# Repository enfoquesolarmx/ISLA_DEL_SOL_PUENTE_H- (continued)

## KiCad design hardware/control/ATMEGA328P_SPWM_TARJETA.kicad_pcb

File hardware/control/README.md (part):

# Tarjeta de control V0.1: el cerebro de la Isla del Sol

La tarjeta de control lleva **dos microcontroladores** (módulos Arduino Nano con ATmega328P) y todo lo que necesitan alrededor:
- la alimentación de 48 V a 15, 8 y 5 V;
- los sensores de voltaje, corriente y temperatura;
- el corte del PWM por hardware;
- las órdenes a la tarjeta de transferencia;
- el CAN con el BMS, la pantalla, el ventilador y el buzzer.

> **Para quien arma y repara en la trinchera:** este documento es un **glosario de módulos**. Cada bloque de la tarjeta dice **qué hace**, **por qué existe**, **por qué cada pieza tiene ese valor** y **qué pasa si esa pieza falla**. Cuando algo no funcione, busca el bloque, mide en su test point y compara con la tabla.

*Vista superior en 3D (KiCad 9), serigrafía "TARJETA DE CONTROL SPWM · ISLA DEL SOL · VER 0.1.J.G NOV 2026". Los dos microcontroladores van en zócalo (aquí se ven los zócalos vacíos), igual que el 74HC08. La serigrafía indica el uso de cada conector, los valores de referencia y los sustitutos de trinchera.*

*Esquemático por bloques (KiCad 9, hoja A2). Cada marco azul es uno de los módulos de este glosario.*

---

## 0. Mapa de la tarjeta

| # | Módulo | Microcontrolador | Decisión | En una frase |
| --- | --- | --- | --- | --- |
| 1 | [Microcontroladores CRÍTICO y AUX](#1-microcontroladores-crítico-y-aux) · [**Mapa de pines**](#11-mapa-de-pines) | — | DC-010, DC-012, DC-017 | El CRÍTICO genera la onda y protege; el AUX informa y conversa |
| 2 | [Entrada de 48 V y su protección](#2-entrada-de-48-v-y-su-protección) | — | DC-003 | Que un pico de la batería no queme el buck |
| 3 | [Buck 48 → 15 V (XL7015)](#3-buck-48--15-v-xl7015) | — | DC-002 | El riel de drivers, relés y ventilador |
| 4 | [Buck 15 → 8 V (MP1584)](#4-buck-15--8-v-mp1584) | — | DC-004 | Baja el voltaje para que el 7805 vaya frío |
| 5 | [Regulador 5 V (7805)](#5-regulador-5-v-7805) | — | DC-005 | 5 V limpio: es la referencia del ADC |
| 6 | [Tablero de LEDs y test points](#6-tablero-de-leds-y-test-points) | — | DC-008 | Dónde está la falla y qué tan mal está |
| 7 | [Monitor del riel de 15 V](#7-monitor-del-riel-de-15-v) | AUX (A1) | DC-008 | Ve envejecer la fuente antes de que falle |
| 8 | [Sensado AC del inversor](#8-sensado-ac-del-inversor-y-de-la-red) | CRÍTICO (A0) | DC-006 | Lazo de amplitud de la salida |
| 9 | [Sensado AC de la red](#8-sensado-ac-del-inversor-y-de-la-red) | CRÍTICO (A6) | DC-006 | Sincronía antes de transferir |
| 10 | [Corriente AC con pinza SCT-013](#9-corriente-ac-con-pinza-sct-013-015) | CRÍTICO (A2) | DC-013 | Watts, sobrecarga y tiempo muerto |
| 11 | [Voltaje de batería](#10-voltaje-de-batería) | CRÍTICO (A3) | DC-007 | Bajo voltaje y estado de carga |
| 12 | [Temperatura (NTC)](#11-temperatura-ntc-10-k) | CRÍTICO (A1) | — | Derrateo y paro por calor |
| 13 | [Corte del PWM por hardware](#12-corte-del-pwm-por-hardware) | CRÍTICO / AUX | DC-014 | Apaga los MOSFET sin esperar al firmware |
| 14 | [Lectura de P9](#13-lectura-de-p9-tiempo-muerto) | CRÍTICO (A7) | DC-011 | Qué gate driver hay y qué tiempo muerto pide |
| 15 | [Límite de corriente I_LIM](#14-límite-de-corriente-i_lim) | CRÍTICO (D2) | DC-016 | Deja arrancar motores sin disparar el corte |
| 16 | [Órdenes a la tarjeta de transferencia (J15)](#15-órdenes-a-la-tarjeta-de-transferencia-j15) | CRÍTICO (D4–D6) | DC-019 | Red, inversor, cargador y unión N–PE |
| 17 | [Caída automática a la red](#16-caída-automática-a-la-red) | — | DC-019 | Si el inversor se corta, la casa vuelve a la red sola |
| 18 | [CAN con el BMS](#17-can-con-el-bms) | AUX (SPI) | DC-010 | Lo que la batería permite cargar y descargar |
| 19 | [Pantalla LCD y botonera](#18-pantalla-lcd-162-y-botonera) | AUX (D4, D5, A7) | — | Menú del SETUP y estado |
| 20 | [Ventilador](#19-ventilador) | AUX (D6) | — | Enfría el puente H |
| 21 | [Buzzer y LED de alarma](#20-buzzer-y-led-de-alarma) | AUX (D8) | — | Avisa sin que nadie mire la pantalla |
| 22 | [Salidas de 15 V y 5 V](#21-salidas-de-15-v-y-5-v) | — | — | Alimentan los gate drivers y módulos externos |

**Regla general de las resistencias de 1 kΩ en serie:** casi todas las señales que salen de la tarjeta por un cable pasan por **1 kΩ antes del pin del microcontrolador** (R3, R15, R19, R22, R25, R38, R39, R41). Si el cable se pela contra 15 V o recibe un pico, esa resistencia limita la corriente que entra a los diodos internos del ATmega a unos pocos mA, y el pin sobrevive. **No se quitan "porque sobran".**

**Regla general de las resistencias de 10 kΩ a GND (pull-down) o a 5 V (pull-up):** fijan el estado de una línea cuando nadie la maneja: microcontrolador en reset, cable suelto, módulo ausente. **El estado que fijan es siempre el seguro:** apagado, sin orden o casa en la red.

---

## 1. Microcontroladores CRÍTICO y AUX

> **Lo que decide la onda y la protege vive en un solo microcontrolador. Lo que informa y conversa vive en el otro.** (DC-010)

| Ref. | Valor | Qué hace | Por qué |
| --- | --- | --- | --- |
| **A1** | Arduino Nano (ATmega328P), **CRÍTICO** | SPWM (D9, D10, D11, D3), sensado AC y DC, relés, corte, P9, I_LIM | Todo lo que tiene que ocurrir **dentro del periodo de la portadora** de 24 kHz. No puede depender de un enlace |
| **A2** | Arduino Nano (ATmega328P), **AUX** | CAN/BMS, LCD, botonera, ventilador, buzzer, SENSOR_OK, AUX_KILL, monitor de 15 V | Lo que no es tiempo real. Si se cuelga, la onda sigue y el CRÍTICO protege solo |
| **R10, R11** | 4.7 kΩ a 5 V | Pull-ups del enlace I2C entre los dos (A4/A5) | El I2C es de drenaje abierto: sin pull-up nunca sube. 4.7 kΩ da un flanco de ~0.4 µs (máximo permitido 1 µs a 100 kHz). **Un solo par para todo el bus** |
| **C15, C19** | 1 µF | Desacople junto al pin +5V de cada Nano | Los Nano se alimentan por **+5V (pin 27), nunca por VIN** (DC-012): VIN pasa por otro regulador que necesita ≥7 V. El 1 µF da la corriente de los picos de conmutación del chip |

- **Los dos van en zócalo:** se cambian sin soldar, y el mismo zócalo acepta un **Nano Every (ATmega4809)** con otro firmware (DC-017, DC-018).
- **Si el enlace I2C se cae:** el AUX manda un latido cada ~100 ms. Si el CRÍTICO no lo recibe en ~500 ms, **deja de cargar** y sigue protegiendo la batería con su propia lectura.

### 1.1 Mapa de pines

> **Fuente de verdad para el firmware.** Verificado pin por pin contra el esquemático (`ATMEGA328P_SPWM_TARJETA.kicad_sch`, 2026-11-13): cada red de esta tabla es la que tiene el pin en KiCad. Si cambia el esquemático, **se actualiza esta tabla en el mismo cambio**.

**Columnas:**
- **Al encender:** cómo debe quedar el pin desde la primera línea de `setup()`, antes que cualquier otra cosa.
- **Dueño:** el timer o periférico que lo controla; ningún otro módulo del firmware debe tocarlo.

#### CRÍTICO (A1): tiempo real, SPWM y protección

| Pin | Red (KiCad) | Función | E/S | Al encender | Dueño | Sección |
| --- | --- | --- | --- | --- | --- | --- |
| D0 / D1 | — | Puerto serie (USB, carga del firmware, reporte) | — | Libre para `Serial` | USART | — |
| **D2** | `CRIT_D2_ILIM` | **I_LIM:** 0 V = en el límite de corriente → bajar la modulación | Entrada (INT0) | Entrada, **sin** pull-up interno (R40 externo) | INT0 | [14](#14-límite-de-corriente-i_lim) |
| **D3** | `LB_IN` | **LB:** pierna B, lado bajo (60/50 Hz) → 74HC08 | Salida | **BAJO** | ISR del Timer1 | [12](#12-corte-del-pwm-por-hardware) |
| **D4** | `INV_D4` | **INV_CMD:** la casa pasa al inversor (K4 + K2), vía R39 | Salida | **BAJO** (casa en la red) | Lógica de transferencia | [15](#15-órdenes-a-la-tarjeta-de-transferencia-j15), [16](#16-caída-automática-a-la-red) |
| **D5** | `CARG_CMD` | **CARG_CMD:** el transformador se conecta a la red para cargar (K1 + K3) | Salida | **BAJO** | Lógica de transferencia | [15](#15-órdenes-a-la-tarjeta-de-transferencia-j15) |
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
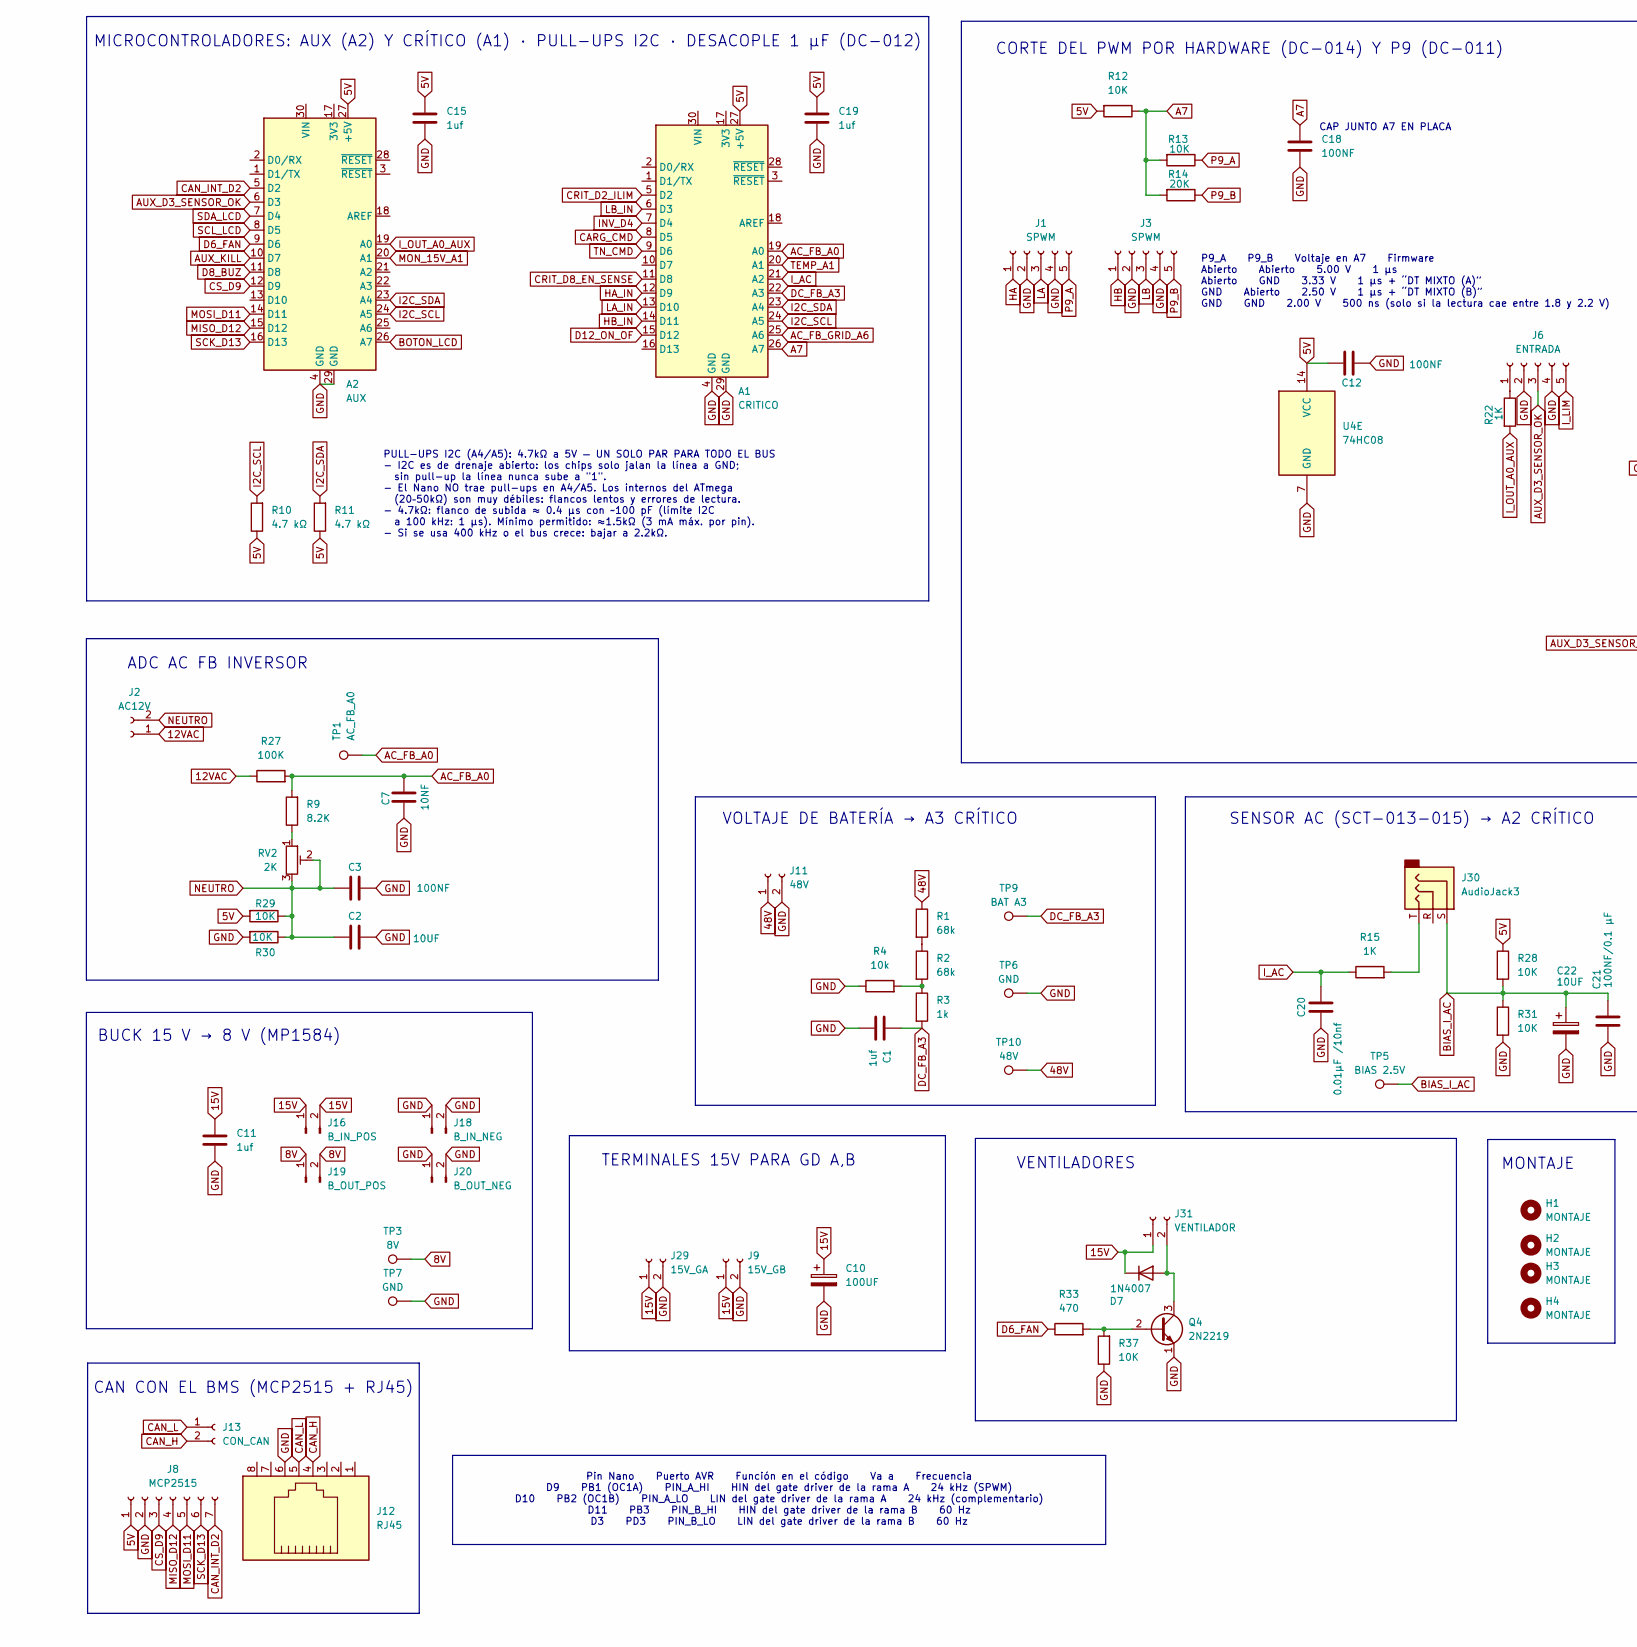
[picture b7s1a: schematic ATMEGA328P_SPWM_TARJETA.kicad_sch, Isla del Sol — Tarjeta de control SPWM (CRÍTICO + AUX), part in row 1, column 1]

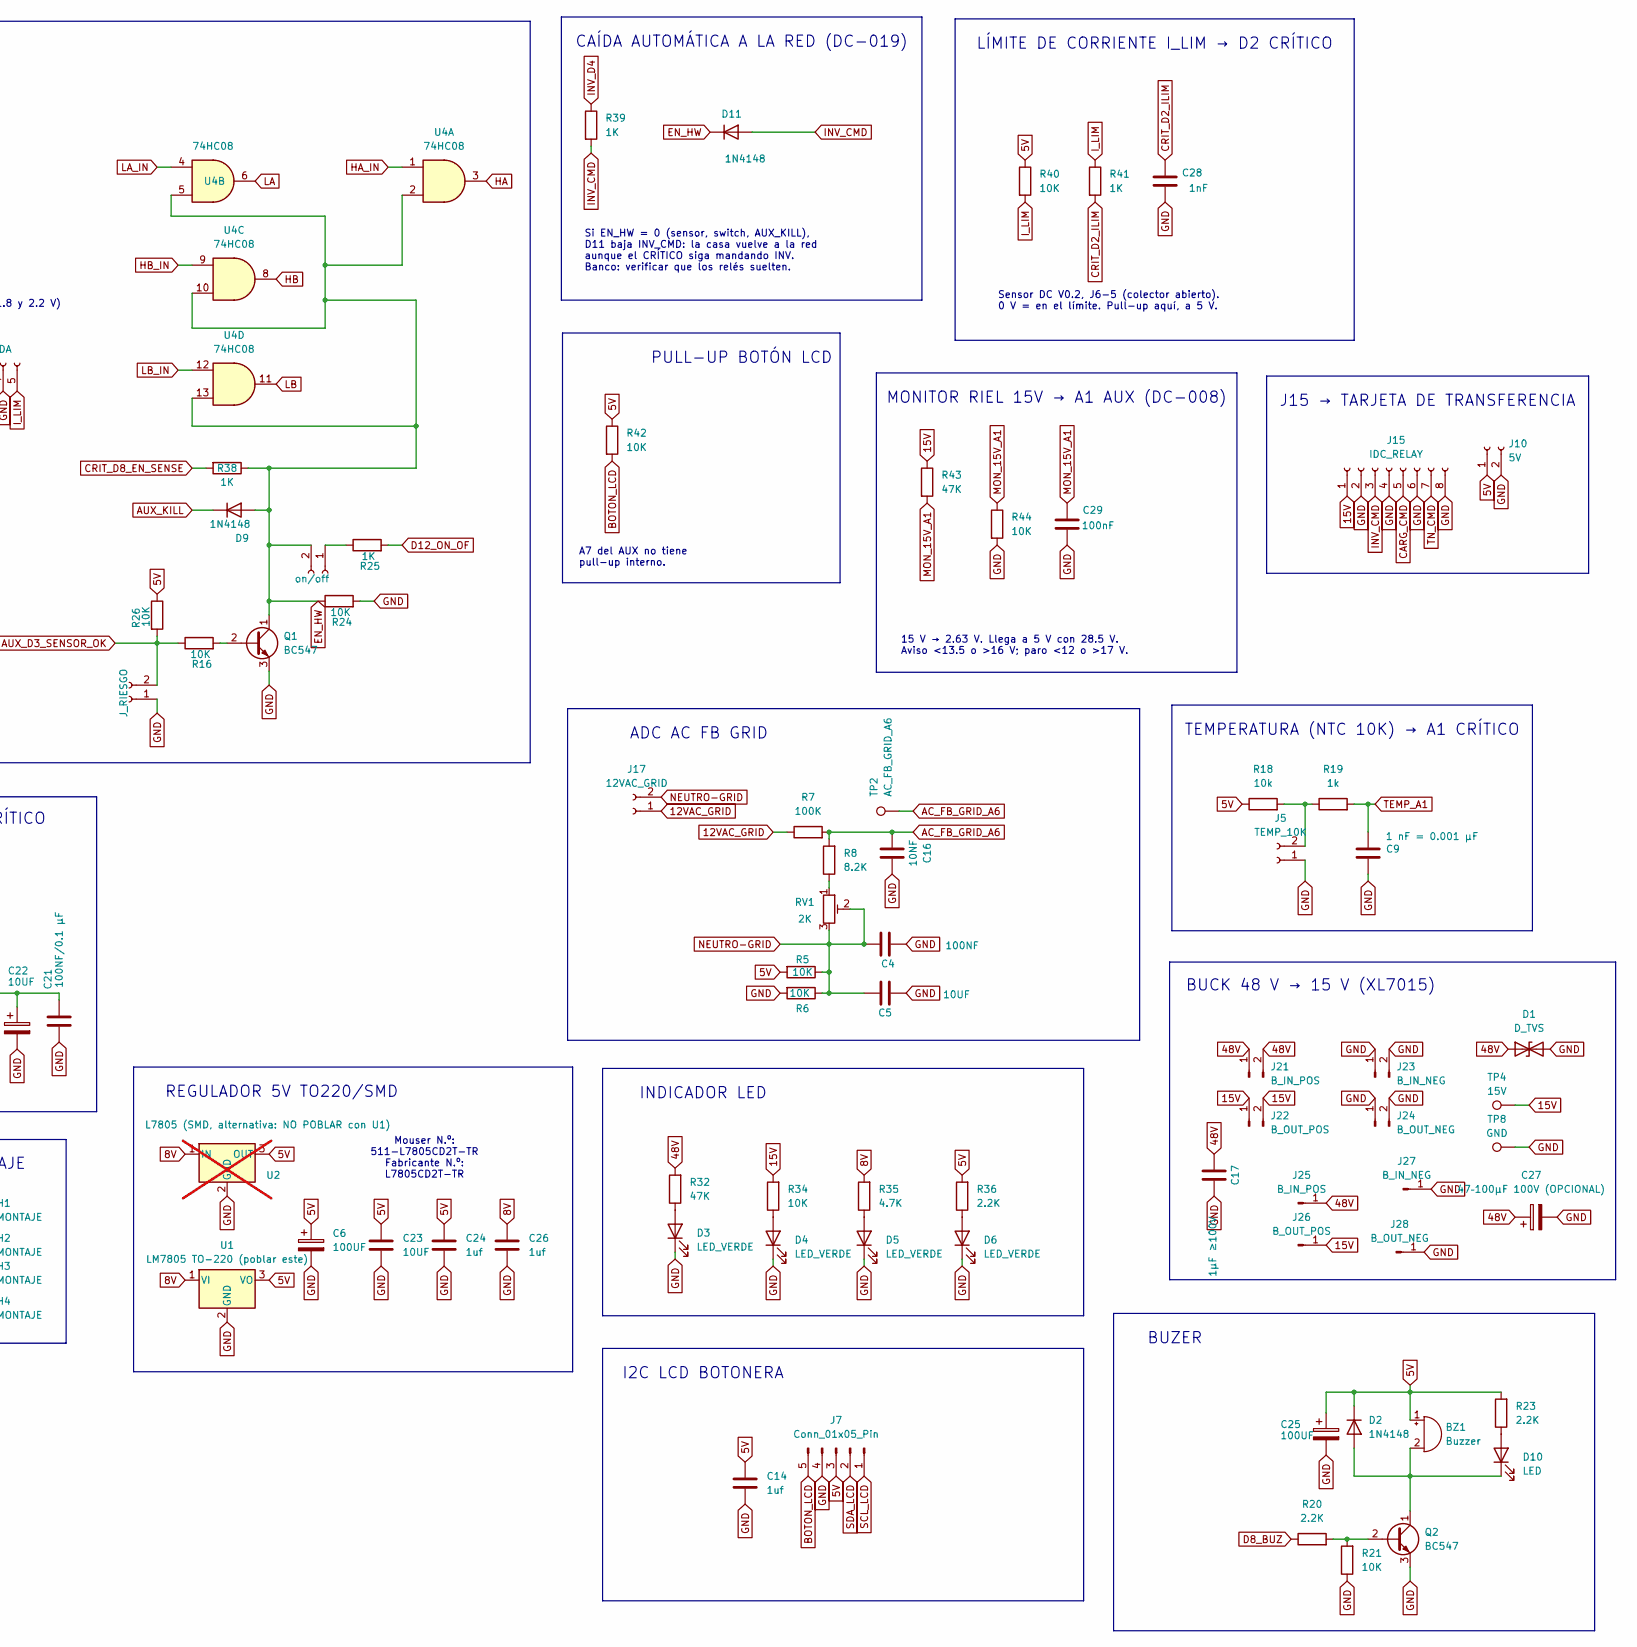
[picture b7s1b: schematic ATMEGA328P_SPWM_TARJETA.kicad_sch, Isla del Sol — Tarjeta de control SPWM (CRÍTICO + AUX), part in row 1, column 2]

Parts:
A1: CRITICO; Arduino_Nano
A2: AUX; Arduino_Nano
BZ1: Buzzer; Buzzer_12x9.5RM7.6
C1, C11, C14, C15, C19, C24, C26: 1uf; C_1206_3216Metric
C2, C5, C23: 10UF; C_1206_3216Metric
C3, C4, C18: 100NF; C_1206_3216Metric
C6, C10: 100UF; CP_Radial_D10.0mm_P5.00mm
C7, C16: 10NF; C_1206_3216Metric
C9: 1 nF = 0.001 µF; C_Disc_D3.0mm_W2.0mm_P2.50mm
C12: 100NF; C_Disc_D3.0mm_W2.0mm_P2.50mm
C17: 1µF ≥100V; C_1210_3225Metric_Pad1.33x2.70mm_HandSolder
C20: 0.01µF /10nf; C_Disc_D3.0mm_W1.6mm_P2.50mm
C21: 100NF/0.1 µF; C_Disc_D3.0mm_W1.6mm_P2.50mm
C22: 10UF; CP_Radial_D8.0mm_P3.50mm
C25: 100UF; CP_Radial_D8.0mm_P3.50mm
C27: 47–100µF 100V (OPCIONAL); CP_Elec_10x10
C28: 1nF; C_Disc_D3.0mm_W2.0mm_P2.50mm
C29: 100nF; C_Disc_D3.0mm_W2.0mm_P2.50mm
D1: D_TVS; D_SMB
D2, D9, D11: 1N4148; D_DO-35_SOD27_P7.62mm_Horizontal
D3, D4, D5, D6: LED_VERDE; LED_1206_3216Metric
D7: 1N4007; D_DO-41_SOD81_P10.16mm_Horizontal
D10: LED; LED_D3.0mm_Clear
H1, H2, H3, H4: MONTAJE; MountingHole_2.7mm_M2.5
J1, J3: SPWM; PhoenixContact_SPT_1.5_5-H-3.5_1x05_P3.5mm_Horizontal
J2: AC12V; TerminalBlock_MaiXu_MX126-5.0-02P_1x02_P5.00mm
J4: on/off; PinHeader_1x02_P2.54mm_Vertical
J5: TEMP_10K; PinHeader_1x02_P2.54mm_Vertical
J6: ENTRADA; PhoenixContact_SPT_1.5_5-H-3.5_1x05_P3.5mm_Horizontal
J7: Conn_01x05_Pin; PinHeader_1x05_P2.54mm_Vertical
J8: MCP2515; PinHeader_1x07_P2.54mm_Vertical
J9: 15V_GB; JST_EH_B2B-EH-A_1x02_P2.50mm_Vertical
J10: 5V; JST_EH_B2B-EH-A_1x02_P2.50mm_Vertical
J11: 48V; TerminalBlock_MaiXu_MX126-5.0-02P_1x02_P5.00mm
J12: RJ45; RJ45_OST_PJ012-8P8CX_Vertical
J13: CON_CAN; PinHeader_1x02_P2.54mm_Vertical
J14: J_RIESGO; PinHeader_1x02_P2.54mm_Vertical
J15: IDC_RELAY; IDC-Header_2x04_P2.54mm_Vertical
J16, J21: B_IN_POS; PinHeader_1x02_P2.54mm_Vertical
J17: 12VAC_GRID; TerminalBlock_MaiXu_MX126-5.0-02P_1x02_P5.00mm
J18, J23: B_IN_NEG; PinHeader_1x02_P2.54mm_Vertical
J19, J22: B_OUT_POS; PinHeader_1x02_P2.54mm_Vertical
J20, J24: B_OUT_NEG; PinHeader_1x02_P2.54mm_Vertical
J25: B_IN_POS; PinHeader_1x01_P2.54mm_Vertical
J26: B_OUT_POS; PinHeader_1x01_P2.54mm_Vertical
J27: B_IN_NEG; PinHeader_1x01_P2.54mm_Vertical
J28: B_OUT_NEG; PinHeader_1x01_P2.54mm_Vertical
J29: 15V_GA; JST_EH_B2B-EH-A_1x02_P2.50mm_Vertical
J30: AudioJack3; Jack_3.5mm_CUI_SJ1-3533NG_Horizontal_CircularHoles
J31: VENTILADOR; JST_EH_B2B-EH-A_1x02_P2.50mm_Vertical
Q1: BC547; TO-92_Inline
Q2: BC547; TO-92_Inline_Wide
Q4: 2N2219; TO-39-3
R1, R2: 68k; R_Axial_DIN0204_L3.6mm_D1.6mm_P5.08mm_Horizontal
R3, R19: 1k; R_Axial_DIN0204_L3.6mm_D1.6mm_P5.08mm_Horizontal
R4, R18: 10k; R_Axial_DIN0204_L3.6mm_D1.6mm_P5.08mm_Horizontal
R5, R6, R12, R13, R16, R21, R24, R26, R28, R29, R30, R31, R34, R37, R40, R42, R44: 10K; R_Axial_DIN0204_L3.6mm_D1.6mm_P5.08mm_Horizontal
R7, R27: 100K; R_Axial_DIN0204_L3.6mm_D1.6mm_P5.08mm_Horizontal
R8, R9: 8.2K; R_Axial_DIN0204_L3.6mm_D1.6mm_P5.08mm_Horizontal
R10, R11: 4.7 kΩ; R_Axial_DIN0204_L3.6mm_D1.6mm_P5.08mm_Horizontal
R14: 20K; R_Axial_DIN0204_L3.6mm_D1.6mm_P5.08mm_Horizontal
R15, R22, R25, R38, R39, R41: 1K; R_Axial_DIN0204_L3.6mm_D1.6mm_P5.08mm_Horizontal
R20, R23, R36: 2.2K; R_Axial_DIN0204_L3.6mm_D1.6mm_P5.08mm_Horizontal
R32, R43: 47K; R_Axial_DIN0204_L3.6mm_D1.6mm_P5.08mm_Horizontal
R33: 470; R_Axial_DIN0204_L3.6mm_D1.6mm_P5.08mm_Horizontal
R35: 4.7K; R_Axial_DIN0204_L3.6mm_D1.6mm_P5.08mm_Horizontal
RV1, RV2: 2K; Potentiometer_Bourns_3296W_Vertical
TP1: AC_FB_A0; TestPoint_Loop_D2.50mm_Drill1.0mm_LowProfile
TP2: AC_FB_GRID_A6; TestPoint_Loop_D2.50mm_Drill1.0mm_LowProfile
TP3: 8V; TestPoint_Loop_D2.50mm_Drill1.0mm_LowProfile
TP4: 15V; TestPoint_Loop_D2.50mm_Drill1.0mm_LowProfile
TP5: BIAS 2.5V; TestPoint_Loop_D2.50mm_Drill1.0mm_LowProfile
TP6, TP7, TP8: GND; TestPoint_Loop_D2.50mm_Drill1.0mm_LowProfile
TP9: BAT A3; TestPoint_Loop_D2.50mm_Drill1.0mm_LowProfile
TP10: 48V; TestPoint_Loop_D2.50mm_Drill1.0mm_LowProfile
U1: LM7805 TO-220 (poblar este); TO-220-3_Horizontal_TabDown
U2: L7805 (SMD, alternativa: NO POBLAR con U1); TO-252-2; not fitted
U4: 74HC08; DIP-14_W7.62mm_Socket

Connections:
5V: A1.27 (+5V), A2.27 (+5V), BZ1.1 (+), C6.1, C12.1, C14.1, C15.1, C19.1, C23.1, C24.1, C25.1, D2.1 (K), J7.3, J8.1, J10.1, R5.2, R10.1, R11.1, R12.2, R18.1, R23.2, R26.1, R28.1, R29.2, R36.2, R40.1, R42.1, U1.3 (VO), U2.3 (OUT), U4.14 (VCC)
8V: C26.1, J19.1, J19.2, R35.2, TP3.1, U1.1 (VI), U2.1 (IN)
12VAC: J2.1, R27.1
12VAC_GRID: J17.1, R7.1
15V: C10.1, C11.1, D7.1 (K), J9.1, J15.1, J16.1, J16.2, J22.1, J22.2, J26.1, J29.1, J31.1, R34.2, R43.1, TP4.1
48V: C17.1, C27.1, D1.1 (A1), J11.1, J21.1, J21.2, J25.1, R1.1, R32.2, TP10.1
A7: A1.26 (A7), C18.1, R12.1, R13.2, R14.2
AC_FB_A0: A1.19 (A0), C7.1, R9.2, R27.2, TP1.1
AC_FB_GRID_A6: A1.25 (A6), C16.1, R7.2, R8.2, TP2.1
AUX_D3_SENSOR_OK: A2.6 (D3), J6.3, J14.2, R16.1, R26.2
AUX_KILL: A2.10 (D7), D9.1 (K)
BIAS_I_AC: C21.1, C22.1, J30.S, R28.2, R31.1, TP5.1
BOTON_LCD: A2.26 (A7), J7.5, R42.2
CAN_H: J12.4, J13.2
CAN_INT_D2: A2.5 (D2), J8.7
CAN_L: J12.5, J13.1
CARG_CMD: A1.8 (D5), J15.5
CRIT_D2_ILIM: A1.5 (D2), C28.1, R41.2
CRIT_D8_EN_SENSE: A1.11 (D8), R38.2
CS_D9: A2.12 (D9), J8.3
D6_FAN: A2.9 (D6), R33.1
D8_BUZ: A2.11 (D8), R20.1
D12_ON_OF: A1.15 (D12), R25.2
DC_FB_A3: A1.22 (A3), C1.1, R3.2, TP9.1
EN_HW: D9.2 (A), D11.1 (K), J4.2, Q1.1 (C), R24.1, R38.1, U4.2, U4.5, U4.10, U4.13
GND: A1.4 (GND), A1.29 (GND), A2.4 (GND), A2.29 (GND), C1.2, C2.2, C3.2, C4.2, C5.2, C6.2, C7.2, C9.2, C10.2, C11.2, C12.2, C14.2, C15.2, C16.2, C17.2, C18.2, C19.2, C20.2, C21.2, C22.2, C23.2, C24.2, C25.2, C26.2, C27.2, C28.2, C29.2, D1.2 (A2), D3.1 (K), D4.1 (K), D5.1 (K), D6.1 (K), J1.2, J1.4, J3.2, J3.4, J5.1, J6.2, J6.4, J7.4, J8.2, J9.2, J10.2, J11.2, J12.6, J14.1, J15.2, J15.4, J15.6, J15.8, J18.1, J18.2, J20.1, J20.2, J23.1, J23.2, J24.1, J24.2, J27.1, J28.1, J29.2, Q1.3 (E), Q2.3 (E), Q4.1 (E), R4.1, R6.2, R21.1, R24.2, R30.2, R31.2, R37.1, R44.2, TP6.1, TP7.1, TP8.1, U1.2 (GND), U2.2 (GND), U4.7 (GND)
HA: J1.1, U4.3
HA_IN: A1.12 (D9), U4.1
HB: J3.1, U4.8
HB_IN: A1.14 (D11), U4.9
I2C_SCL: A1.24 (A5), A2.24 (A5), R10.2
I2C_SDA: A1.23 (A4), A2.23 (A4), R11.2
INV_CMD: D11.2 (A), J15.3, R39.2
INV_D4: A1.7 (D4), R39.1
I_AC: A1.21 (A2), C20.1, R15.1
I_LIM: J6.5, R40.2, R41.1
I_OUT_A0_AUX: A2.19 (A0), R22.2
LA: J1.3, U4.6
LA_IN: A1.13 (D10), U4.4
LB: J3.3, U4.11
LB_IN: A1.6 (D3), U4.12
MISO_D12: A2.15 (D12), J8.4
MON_15V_A1: A2.20 (A1), C29.1, R43.2, R44.1
MOSI_D11: A2.14 (D11), J8.5
NEUTRO: C2.1, C3.1, J2.2, R29.1, R30.1, RV2.2, RV2.3
NEUTRO-GRID: C4.1, C5.1, J17.2, R5.1, R6.1, RV1.2, RV1.3
unnamed: BZ1.2 (-), D2.2 (A), D10.1 (K), Q2.1 (C)
unnamed: D3.2 (A), R32.1
unnamed: D4.2 (A), R34.1
unnamed: D5.2 (A), R35.1
unnamed: D6.2 (A), R36.1
unnamed: D7.2 (A), J31.2, Q4.3 (C)
unnamed: D10.2 (A), R23.1
unnamed: J4.1, R25.1
unnamed: J5.2, R18.2, R19.1
unnamed: J6.1, R22.1
unnamed: J30.T, R15.2
unnamed: Q1.2 (B), R16.2
unnamed: Q2.2 (B), R20.2, R21.2
unnamed: Q4.2 (B), R33.2, R37.2
unnamed: R1.2, R2.1
unnamed: R2.2, R3.1, R4.2
unnamed: R8.1, RV1.1
unnamed: R9.1, RV2.1
P9_A: J1.5, R13.1
P9_B: J3.5, R14.1
SCK_D13: A2.16 (D13), J8.6
SCL_LCD: A2.8 (D5), J7.1
SDA_LCD: A2.7 (D4), J7.2
TEMP_A1: A1.20 (A1), C9.1, R19.2
TN_CMD: A1.9 (D6), J15.7

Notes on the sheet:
MONTAJE
TERMINALES 15V PARA GD A,B
Mouser N.º: 511-L7805CD2T-TR Fabricante N.º: L7805CD2T-TR
BUZER
P9_A P9_B Voltaje en A7 Firmware Abierto Abierto 5.00 V 1 µs Abierto GND 3.33 V 1 µs + “DT MIXTO (A)” GND Abierto 2.50 V 1 µs + “DT MIXTO (B)” GND GND 2.00 V 500 ns (solo si la lectura cae entre 1.8 y 2.2 V)
MONITOR RIEL 15V → A1 AUX (DC-008)
REGULADOR 5V TO220/SMD
PULL-UP BOTÓN LCD
BUCK 15 V → 8 V (MP1584)
ADC AC FB GRID
MICROCONTROLADORES: AUX (A2) Y CRÍTICO (A1) · PULL-UPS I2C · DESACOPLE 1 µF (DC-012)
CAÍDA AUTOMÁTICA A LA RED (DC-019)
CORTE DEL PWM POR HARDWARE (DC-014) Y P9 (DC-011)
CAN CON EL BMS (MCP2515 + RJ45)
BUCK 48 V → 15 V (XL7015)
J15 → TARJETA DE TRANSFERENCIA
VOLTAJE DE BATERÍA → A3 CRÍTICO
Si EN_HW = 0 (sensor, switch, AUX_KILL), D11 baja INV_CMD: la casa vuelve a la red aunque el CRÍTICO siga mandando INV. Banco: verificar que los relés suelten.
VENTILADORES
PULL-UPS I2C (A4/A5): 4.7kΩ a 5V — UN SOLO PAR PARA TODO EL BUS - I2C es de drenaje abierto: los chips solo jalan la línea a GND; sin pull-up la línea nunca sube a "1". - El Nano NO trae pull-ups en A4/A5. Los internos del ATmega (20–50kΩ) son muy débiles: flancos lentos y errores de lectura. - 4.7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
CAP JUNTO A7 EN PLACA
Sensor DC V0.2, J6-5 (colector abierto). 0 V = en el límite. Pull-up aquí, a 5 V.
SENSOR AC (SCT-013-015) → A2 CRÍTICO
A7 del AUX no tiene pull-up interno.
I2C LCD BOTONERA
ADC AC FB INVERSOR
LÍMITE DE CORRIENTE I_LIM → D2 CRÍTICO
Pin Nano Puerto AVR Función en el código Va a Frecuencia D9 PB1 (OC1A) PIN_A_HI HIN del gate driver de la rama A 24 kHz (SPWM) D10 PB2 (OC1B) PIN_A_LO LIN del gate driver de la rama A 24 kHz (complementario) D11 PB3 PIN_B_HI HIN del gate driver de la rama B 60 Hz D3 PD3 PIN_B_LO LIN del gate driver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
15 V → 2.63 V. Llega a 5 V con 28.5 V. Aviso <13.5 o >16 V; paro <12 o >17 V.
TEMPERATURA (NTC 10K) → A1 CRÍTICO
INDICADOR LED

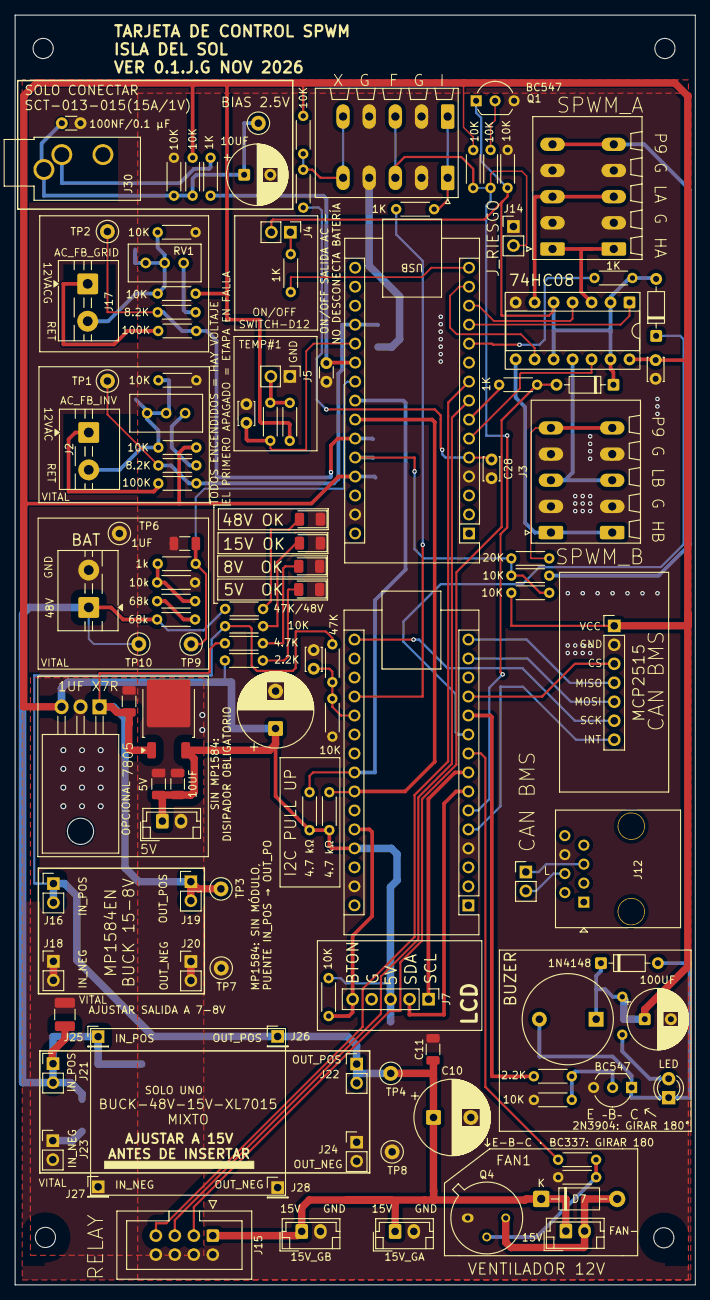
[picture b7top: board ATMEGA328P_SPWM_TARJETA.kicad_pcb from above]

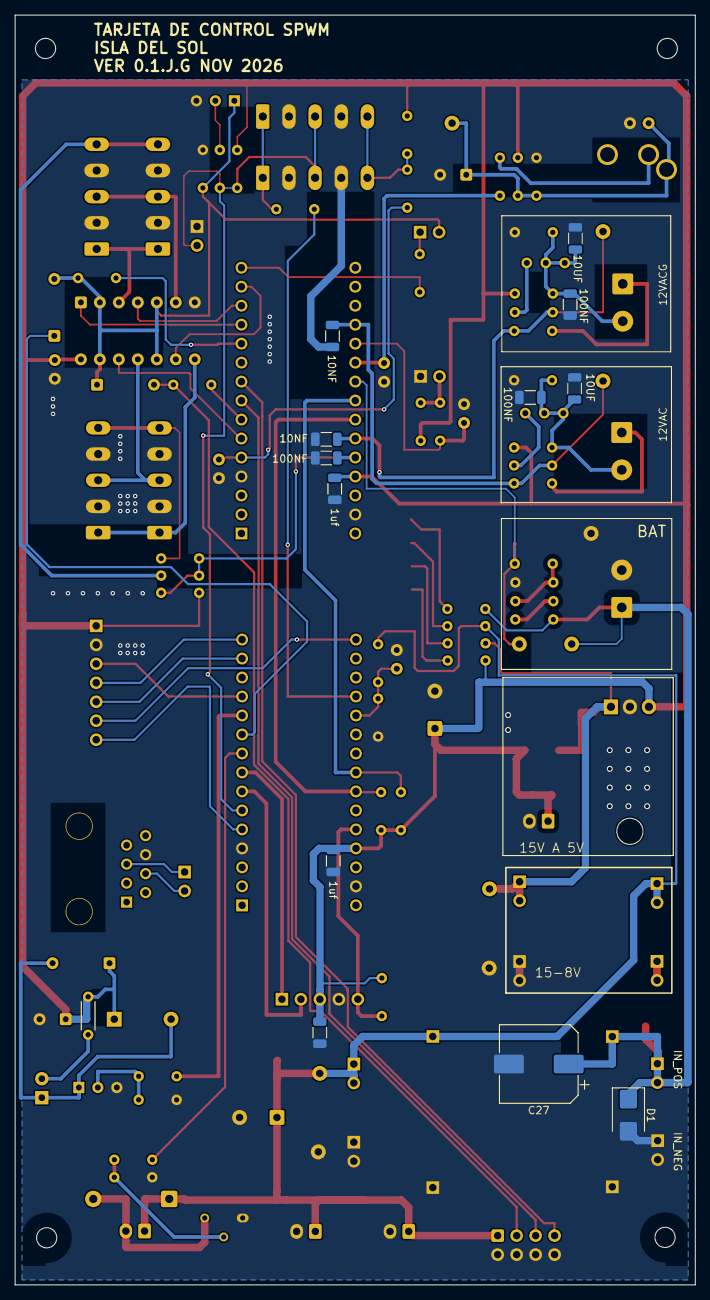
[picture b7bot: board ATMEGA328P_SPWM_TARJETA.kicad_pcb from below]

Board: 2 copper layers, 91.0 x 169.9 mm, 136 parts (13 on the bottom side), 71 nets.

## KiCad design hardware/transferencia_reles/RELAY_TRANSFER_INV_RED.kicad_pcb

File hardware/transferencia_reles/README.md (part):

# Tarjeta de transferencia de carga V0.1: 5 relés (red · inversor · cargador)

Tarjeta de potencia de 127 V que decide **de dónde se alimenta la casa**: de la **red** o del **inversor**. También conecta el **transformador a la red para cargar la batería** y hace la **unión neutro–tierra (N–PE)** cuando el inversor es la fuente principal.

Recibe tres órdenes de la tarjeta de control por un cable plano IDC de 8 hilos (J15) y no tiene microcontrolador propio. **Si se va la energía de 15 V, se suelta el cable o el microcontrolador de la tarjeta de control está en reset, todos los relés se sueltan y la casa queda en la red** (falla segura).

> ⚠️ **127 V AC en bornes, pistas y contactos de relé: pueden ser mortales.** Prototipo en desarrollo, no certificado. La decisión de diseño completa está en [DC-019](../../docs/decisiones_criticas.md) y el estudio de referencia industrial en [OutBack FX](../../docs/referencia_outback_fx.md).

*Render 3D de KiCad 9, V0.1. Arriba, la lógica de 15 V (J15, ULN2003A, Q1/Q2) y el título; abajo, los 5 relés, los bornes de 127 V y los capacitores X2/Y2. El modelo de los relés es aproximado (`3d/`).*

---

## 0. Por qué la Isla del Sol necesita esta tarjeta

La Isla del Sol es **inversor y cargador a la vez**: el mismo puente H y el **mismo transformador** sacan 127 V de la batería cuando no hay red, y la cargan desde la **red eléctrica pública** (o un generador) cuando sí hay. Ese doble papel deja tres preguntas que el puente H no puede contestar por sí solo y que esta tarjeta resuelve **con hardware**:

**1. ¿De dónde se alimenta la casa, y cómo se garantiza que nunca sea de las dos fuentes a la vez?**
Si la salida del inversor queda en paralelo con la red, aunque sea un instante:
- la red eléctrica alimenta de reversa al transformador y al puente H y lo destruye (son dos fuentes de 127 V que no están sincronizadas);
- con la red caída, el inversor **energiza la acometida**: 127 V en las líneas de la red eléctrica, donde puede haber un liniero trabajando.

Por eso la transferencia la hace un **conmutador de 2 polos y 2 tiros** (K4 + K2): el mismo contacto que conecta la casa a una fuente la desconecta de la otra. **Ni siquiera un relé soldado forma el paralelo** (análisis de falla en [DC-019](../../docs/decisiones_criticas.md)). Es el principio del equipo de transferencia de los sistemas de respaldo (NOM-001-SEDE-2012 de México, art. 702; equivalente al artículo 702 del NEC de EE. UU.).

**2. ¿Cómo se conecta el transformador a la red para cargar la batería, sin que la casa se quede sin luz?**
En modo cargador, K1 + K3 conectan el transformador al **nodo de la casa**, que sigue en la red por los contactos NC. La casa nunca se queda sin luz mientras se carga, y el candado Q1 impide que "cargar" e "invertir" se pidan al mismo tiempo.

**3. ¿Quién hace la unión neutro–tierra cuando el inversor alimenta la casa?**
Al conmutar también el neutro, el inversor se vuelve un **sistema derivado separadamente**. Necesita su propia unión N–PE (NOM-001-SEDE-2012, 250-30; NEC 250.30), pero **solo** cuando es la fuente: con la red, la unión es la de la acometida, y una segunda unión haría circular corriente por la tierra. K5 la hace de forma automática según el modo del SETUP (sección 4.1). El OutBack FX, la referencia industrial, deja esa decisión al instalador ([estudio](../../docs/referencia_outback_fx.md)).

**Y además, por diseño de la Isla del Sol:**
- **Los 127 V fuera de la tarjeta de control** ([DC-015](../../docs/decisiones_criticas.md)). El microcontrolador, el LCD y los botones solo ven 15 V y un cable plano. Toda la parte de 127 V vive aquí, con 5 mm de separación y ranuras de aislamiento.
- **Falla segura:** sin 15 V, con el cable suelto o con el microcontrolador en reset, la casa queda **en la red**. Si el inversor se apaga por cualquier causa, la casa no se queda a oscuras si hay red.
- **Reparable en la trinchera:** relés de 30 A tipo T90, ULN2003, BC547, 1N4148 y resistencias de agujero pasado. Todo se consigue en una tienda de electrónica local, se cambia con un cautín y está documentado pieza por pieza.

**Dónde se usa:**

| Instalación | Modo normal | Qué hace la tarjeta |
| --- | --- | --- |
| Casa con red inestable (respaldo) | Red | Al fallar la red pasa a inversor (modo CARGA/UPS o CASA); al volver, regresa a la red y carga la batería |
| Sitio aislado con generador | Inversor (CASA) | El generador entra como "red" para cargar la batería y alimentar la casa mientras tanto |
| Solar como fuente principal, red de respaldo | Inversor (CASA) | Usa primero el sol y la batería; la red solo para cargar o cuando la batería se agota |

## 1. Características

| Parámetro | Valor |
| --- | --- |
| Voltaje | 127 V AC / 60 Hz (fase, neutro y tierra física) |
| Corriente de diseño | **10 A RMS continuos** (1270 VA) |
| Relés | 5 × SPDT de 30 A NO / 20 A NC, familia T90. **Bobina de 15 V** (p. ej. Picker PTRH-1C-15S) o Rayex L90S de 12 V con 39 Ω (sección 12) |
| Conmuta | **Fase y neutro** (los dos polos), en transferencia y en cargador |
| Mando | ULN2003A desde 15 V; 3 canales: INV, CARG, TN |
| Candados por hardware | Q1: el inversor bloquea al cargador · Q2: la unión N–PE solo con inversor activo |
| Filtro | C_F 4.7 µF X2 del lado del transformador · CX_RED 0.1 µF X2 + CY_RED 0.1 µF Y2 del lado de la red |
| Versión | **V0.1** (2026-11). En la serigrafía: "ISLA DEL SOL · TARJETA DE TRANSFERENCIA DE CARGA · V0.1.J.G · 2026-11" |
| Placa | 158.4 × 131.1 mm, 2 capas, **1 oz**, 4 barrenos de montaje Ø4.3 mm, **4 ranuras de aislamiento** |
| Separaciones | **≥ 5 mm** de 127 V a lógica · **≥ 3 mm** entre redes de 127 V (verificado con script, secciones 9 y 10) |

## 2. Archivos

| Archivo | Qué es |
| --- | --- |
| `RELAY_TRANSFER_INV_RED.kicad_pro` | Proyecto de KiCad 9 (incluye las exclusiones del DRC: serigrafía sobre las ranuras y las 3 islas unidas por cable) |
| `RELAY_TRANSFER_INV_RED.kicad_sch` | Esquemático, en 5 bloques sobre A3 |
| `RELAY_TRANSFER_INV_RED.kicad_pcb` | Layout |
| `RELAY_TRANSFER_INV_RED.kicad_dru` | **Reglas de separación** de 5 mm y 3 mm para el DRC de KiCad (sección 10). Va en la misma carpeta que el proyecto |
| `auditoria/` | Auditoría térmica a 10 A: script, mapas e informe ([README](auditoria/README.md)) |
| `3d/` | **Modelo 3D aproximado del relé** (`Relay_SPDT_RAYEX-L90S_aprox.step`) y el script que lo genera (CadQuery). KiCad no trae el modelo oficial de esta huella; los relés lo usan con la ruta `${KIPRJMOD}/3d/...` |
| `img/` | Imágenes de este documento |

---

## 3. Cómo funciona

### 3.1 Los relés

Hay dos pares de relés iguales, uno para la **fase (L)** y otro para el **neutro (N)**, más el relé de la unión N–PE.

| Relé | Polo | Función | COM (11) | NC (12), en reposo | NO (14), energizado |
| --- | --- | --- | --- | --- | --- |
| **K4** (K_L2) | L | Transferencia | L-LOAD (casa) | **L-GRID** (red) | L-INV (transformador) |
| **K2** | N | Transferencia | N-LOAD | **N-GRID** | N-INV |
| **K1** (K_L3) | L | Cargador | L-INV | sin conectar | L-LOAD |
| **K3** | N | Cargador | N-INV | sin conectar | N-LOAD |
| **K5** (RL_TN) | N–PE | Unión neutro–tierra | N-INV | sin conectar | TIERRA |

K4 y K2 forman un **conmutador de 2 polos y 2 tiros**: la casa nunca puede tener la red y el inversor al mismo tiempo, porque es el mismo contacto el que cambia de lado.

### 3.2 Los tres canales y los modos

| Canal (salida del ULN2003) | Orden en J15 | Bobinas | LED |
| --- | --- | --- | --- |
| **INV** (AISLAR RED), salida 16 | J15-3 | K4 + K2 | D8 |
| **CARG** (TRAFO), salida 15 | J15-5 | K1 + K3 | D6 |
| **TN**, salida 14 | J15-7, **pasando por Q2** | K5 | D9 |

| Modo | INV | CARG | TN | La casa queda en | El transformador |
| --- | --- | --- | --- | --- | --- |
| **Red** (también: sin 15 V, cable suelto, microcontrolador en reset) | 0 | 0 | 0 | Red | Aislado |
| **Inversor CASA** (fuente principal) | 1 | 0 | 1 | Inversor, **con unión N–PE** (K5) | Alimenta la casa |
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
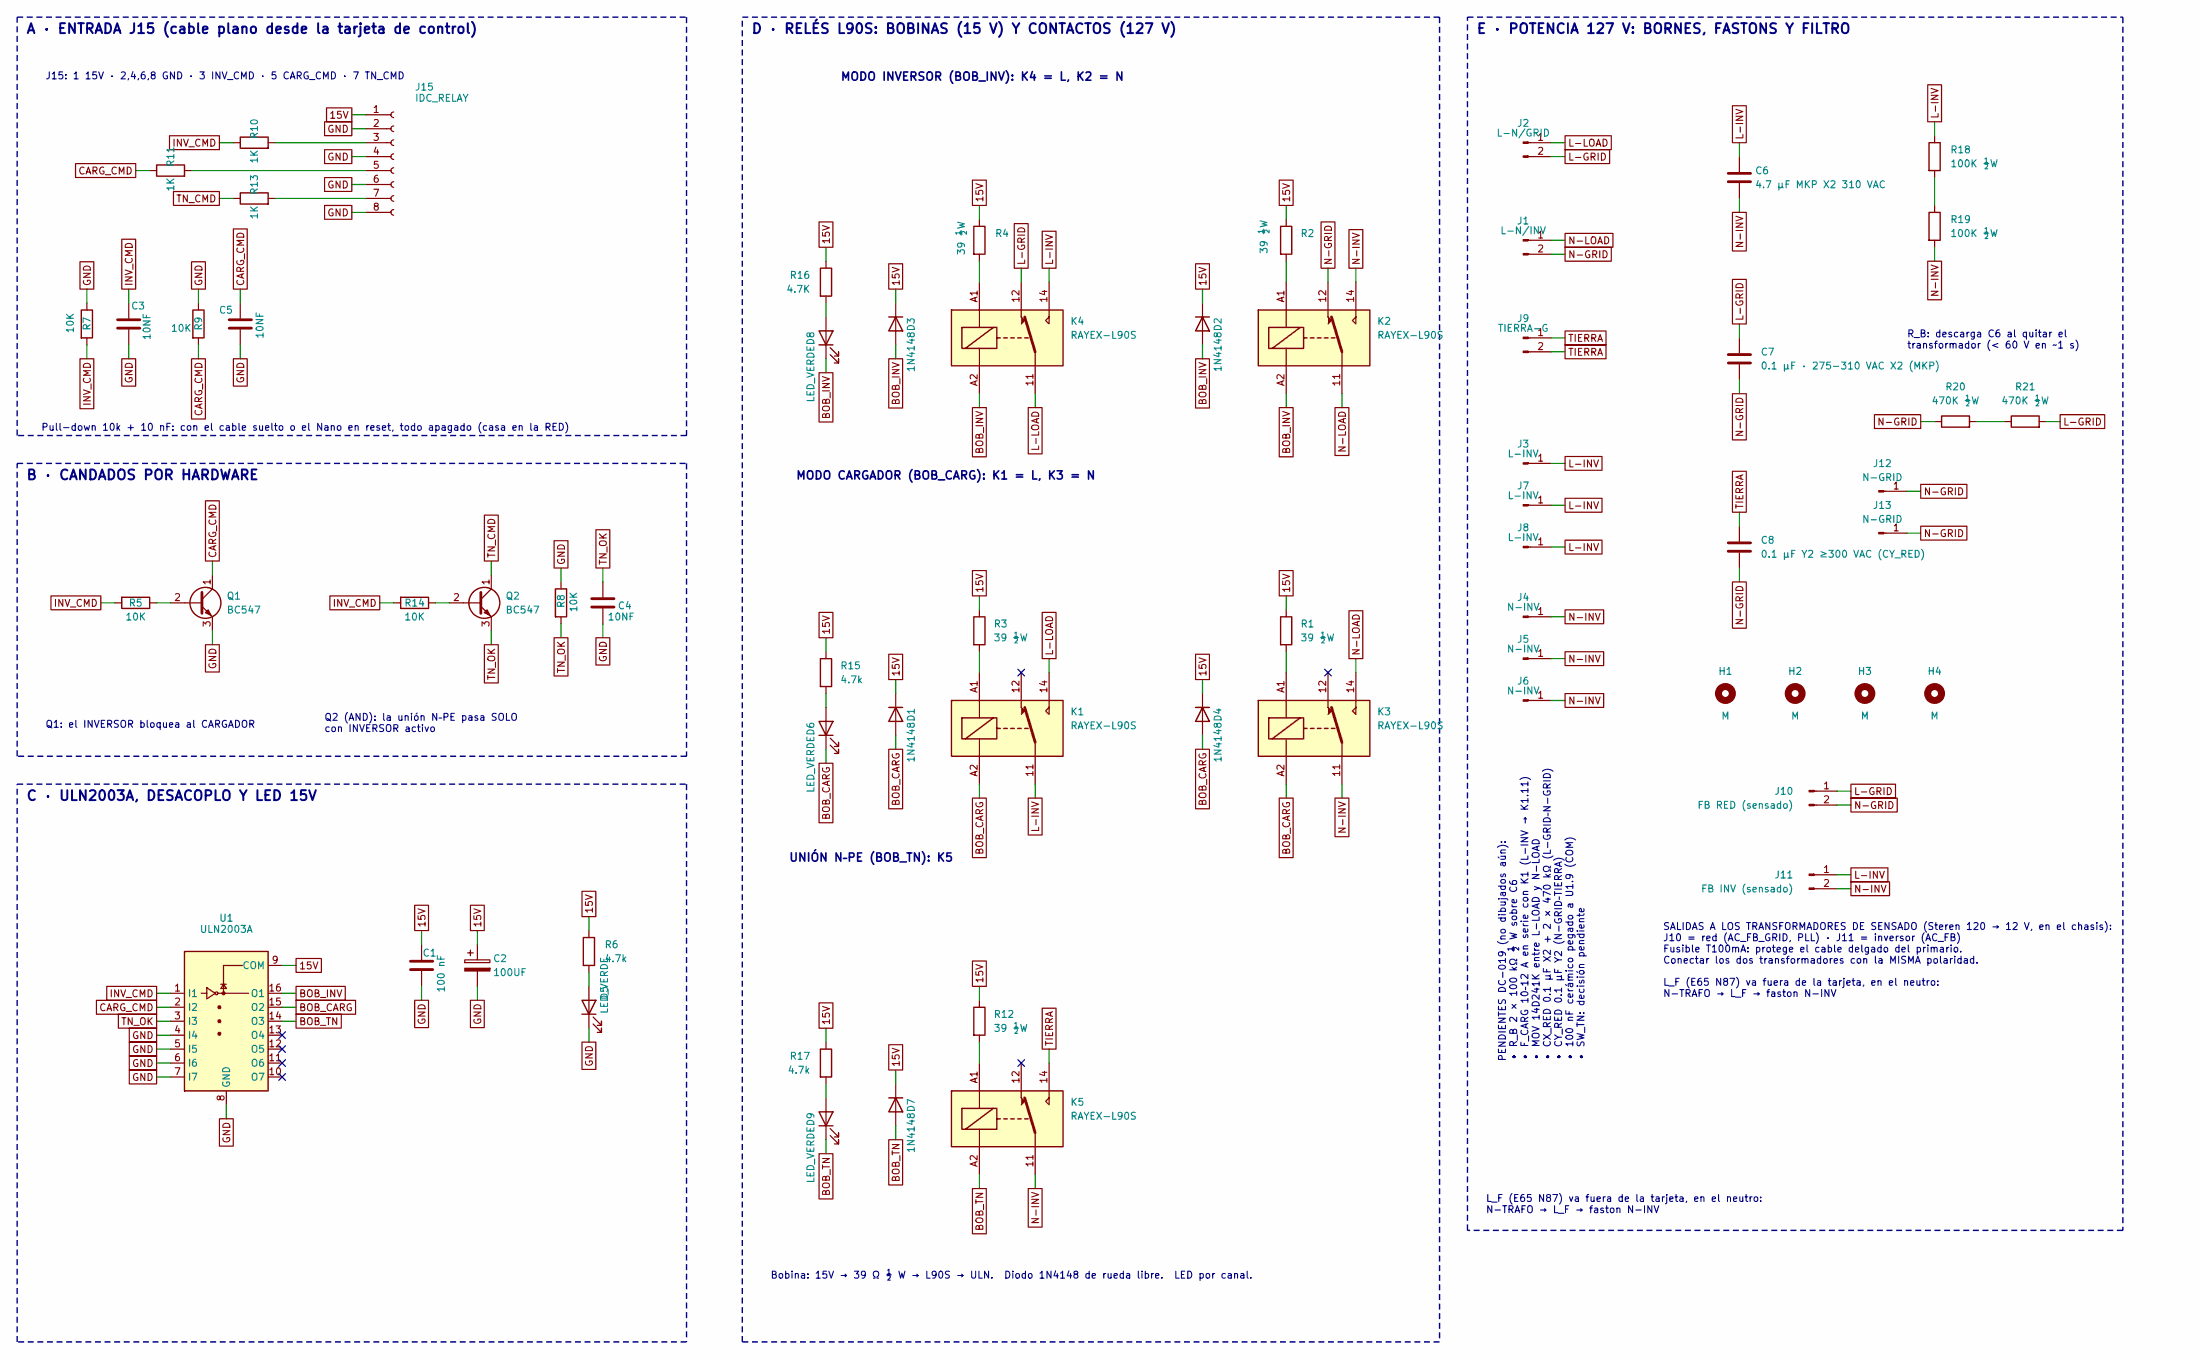
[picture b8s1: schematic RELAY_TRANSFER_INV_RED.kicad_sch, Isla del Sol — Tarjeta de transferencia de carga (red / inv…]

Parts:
C1: 100 nF; C_Disc_D3.0mm_W1.6mm_P2.50mm
C2: 100UF; CP_Radial_D10.0mm_P3.50mm
C3, C4, C5: 10NF; C_Disc_D3.0mm_W1.6mm_P2.50mm
C6: 4.7 µF MKP X2 310 VAC; C_Rect_L31.5mm_W20.0mm_P27.50mm_MKS4
C7: 0.1 µF · 275-310 VAC X2 (MKP); C_Rect_L18.0mm_W6.0mm_P15.00mm_FKS3_FKP3
C8: 0.1 µF Y2 ≥300 VAC (CY_RED); C_Rect_L26.5mm_W8.5mm_P22.50mm_MKS4
D1, D2, D3, D4, D7: 1N4148; D_DO-35_SOD27_P7.62mm_Horizontal
D5, D6, D8, D9: LED_VERDE; LED_D3.0mm
H1, H2, H3, H4: M; MountingHole_4.3mm_M4
J1: L-N/INV; PhoenixContact_SPT_2.5_2-V-5.0-EX_1x02_P5.0mm_Vertical
J2: L-N/GRID; PhoenixContact_SPT_2.5_2-V-5.0-EX_1x02_P5.0mm_Vertical
J3, J8: L-INV; SolderWire-2.5sqmm_1x01_D2.4mm_OD3.6mm_Relief
J4: N-INV; Faston 63823
J5, J6: N-INV; SolderWire-2.5sqmm_1x01_D2.4mm_OD3.6mm_Relief
J7: L-INV; Faston 63823
J9: TIERRA-G; PhoenixContact_SPT_2.5_2-V-5.0-EX_1x02_P5.0mm_Vertical
J10: FB RED (sensado); PhoenixContact_SPT_2.5_2-V-5.0-EX_1x02_P5.0mm_Vertical
J11: FB INV (sensado); PhoenixContact_SPT_2.5_2-V-5.0-EX_1x02_P5.0mm_Vertical
J12, J13: N-GRID; SolderWire-2.5sqmm_1x01_D2.4mm_OD3.6mm
J15: IDC_RELAY; IDC-Header_2x04_P2.54mm_Vertical
K1, K2, K3, K4, K5: RAYEX-L90S; Relay_SPDT_RAYEX-L90S
Q1, Q2: BC547; TO-92_Inline_Wide
R1, R2, R3, R4, R12: 39 ½W; R_Axial_DIN0207_L6.3mm_D2.5mm_P10.16mm_Horizontal
R5, R7, R8, R9, R14: 10K; R_Axial_DIN0204_L3.6mm_D1.6mm_P5.08mm_Horizontal
R6, R15, R17: 4.7k; R_Axial_DIN0204_L3.6mm_D1.6mm_P5.08mm_Horizontal
R10, R11, R13: 1K; R_Axial_DIN0204_L3.6mm_D1.6mm_P5.08mm_Horizontal
R16: 4.7K; R_Axial_DIN0204_L3.6mm_D1.6mm_P5.08mm_Horizontal
R18, R19: 100K ½W; R_Axial_DIN0207_L6.3mm_D2.5mm_P10.16mm_Horizontal
R20, R21: 470K ½W; R_Axial_DIN0207_L6.3mm_D2.5mm_P10.16mm_Horizontal
U1: ULN2003A; DIP-16_W7.62mm

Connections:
15V: C1.2, C2.1, D1.1 (K), D2.1 (K), D3.1 (K), D4.1 (K), D7.1 (K), J15.1, R1.1, R2.1, R3.1, R4.1, R6.1, R12.1, R15.1, R16.1, R17.1, U1.9 (COM)
BOB_CARG: D1.2 (A), D4.2 (A), D6.1 (K), K1.A2, K3.A2, U1.15 (O2)
BOB_INV: D2.2 (A), D3.2 (A), D8.1 (K), K2.A2, K4.A2, U1.16 (O1)
BOB_TN: D7.2 (A), D9.1 (K), K5.A2, U1.14 (O3)
CARG_CMD: C5.2, Q1.1 (C), R9.2, R11.1, U1.2 (I2)
GND: C1.1, C2.2, C3.1, C4.1, C5.1, D5.1 (K), J15.2, J15.4, J15.6, J15.8, Q1.3 (E), R7.1, R8.1, R9.1, U1.4 (I4), U1.5 (I5), U1.6 (I6), U1.7 (I7), U1.8 (GND)
INV_CMD: C3.2, R5.2, R7.2, R10.1, R14.2, U1.1 (I1)
L-GRID: C7.1, J2.2, J10.1, K4.12, R21.2
L-INV: C6.1, J3.1, J7.1, J8.1, J11.1, K1.11, K4.14, R18.1
L-LOAD: J2.1, K1.14, K4.11
N-GRID: C7.2, C8.2, J1.2, J10.2, J12.1, J13.1, K2.12, R20.1
N-INV: C6.2, J4.1, J5.1, J6.1, J11.2, K2.14, K3.11, K5.11, R19.2
N-LOAD: J1.1, K2.11, K3.14
unnamed: D5.2 (A), R6.2
unnamed: D6.2 (A), R15.2
unnamed: D8.2 (A), R16.2
unnamed: D9.2 (A), R17.2
unnamed: J15.3, R10.2
unnamed: J15.5, R11.2
unnamed: J15.7, R13.2
unnamed: K1.A1, R3.2
unnamed: K2.A1, R2.2
unnamed: K3.A1, R1.2
unnamed: K4.A1, R4.2
unnamed: K5.A1, R12.2
unnamed: Q1.2 (B), R5.1
unnamed: Q2.2 (B), R14.1
unnamed: R18.2, R19.1
unnamed: R20.2, R21.1
TIERRA: C8.1, J9.1, J9.2, K5.14
TN_CMD: Q2.1 (C), R13.1
TN_OK: C4.2, Q2.3 (E), R8.2, U1.3 (I3)

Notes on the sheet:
B · CANDADOS POR HARDWARE
E · POTENCIA 127 V: BORNES, FASTONS Y FILTRO
Q1: el INVERSOR bloquea al CARGADOR
Pull-down 10k + 10 nF: con el cable suelto o el Nano en reset, todo apagado (casa en la RED)
J15: 1 15V · 2,4,6,8 GND · 3 INV_CMD · 5 CARG_CMD · 7 TN_CMD
Bobina: 15V → 39 Ω ½ W → L90S → ULN. Diodo 1N4148 de rueda libre. LED por canal.
R_B: descarga C6 al quitar el transformador (< 60 V en ~1 s)
D · RELÉS L90S: BOBINAS (15 V) Y CONTACTOS (127 V)
UNIÓN N–PE (BOB_TN): K5
Q2 (AND): la unión N–PE pasa SOLO con INVERSOR activo
C · ULN2003A, DESACOPLO Y LED 15V
SALIDAS A LOS TRANSFORMADORES DE SENSADO (Steren 120 → 12 V, en el chasis): J10 = red (AC_FB_GRID, PLL) · J11 = inversor (AC_FB) Fusible T100mA: protege el cable delgado del primario. Conectar los dos transformadores con la MISMA polaridad.
MODO CARGADOR (BOB_CARG): K1 = L, K3 = N
MODO INVERSOR (BOB_INV): K4 = L, K2 = N
L_F (E65 N87) va fuera de la tarjeta, en el neutro: N-TRAFO → L_F → faston N-INV
PENDIENTES DC-019 (no dibujados aún): • R_B 2 × 100 kΩ ½ W sobre C6 • F_CARG 10–12 A en serie con K1 (L-INV → K1.11) • MOV 14D241K entre L-LOAD y N-LOAD • CX_RED 0.1 µF X2 + 2 × 470 kΩ (L-GRID–N-GRID) • CY_RED 0.1 µF Y2 (N-GRID–TIERRA) • 100 nF cerámico pegado a U1.9 (COM) • SW_TN: decisión pendien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
A · ENTRADA J15 (cable plano desde la tarjeta de control)
